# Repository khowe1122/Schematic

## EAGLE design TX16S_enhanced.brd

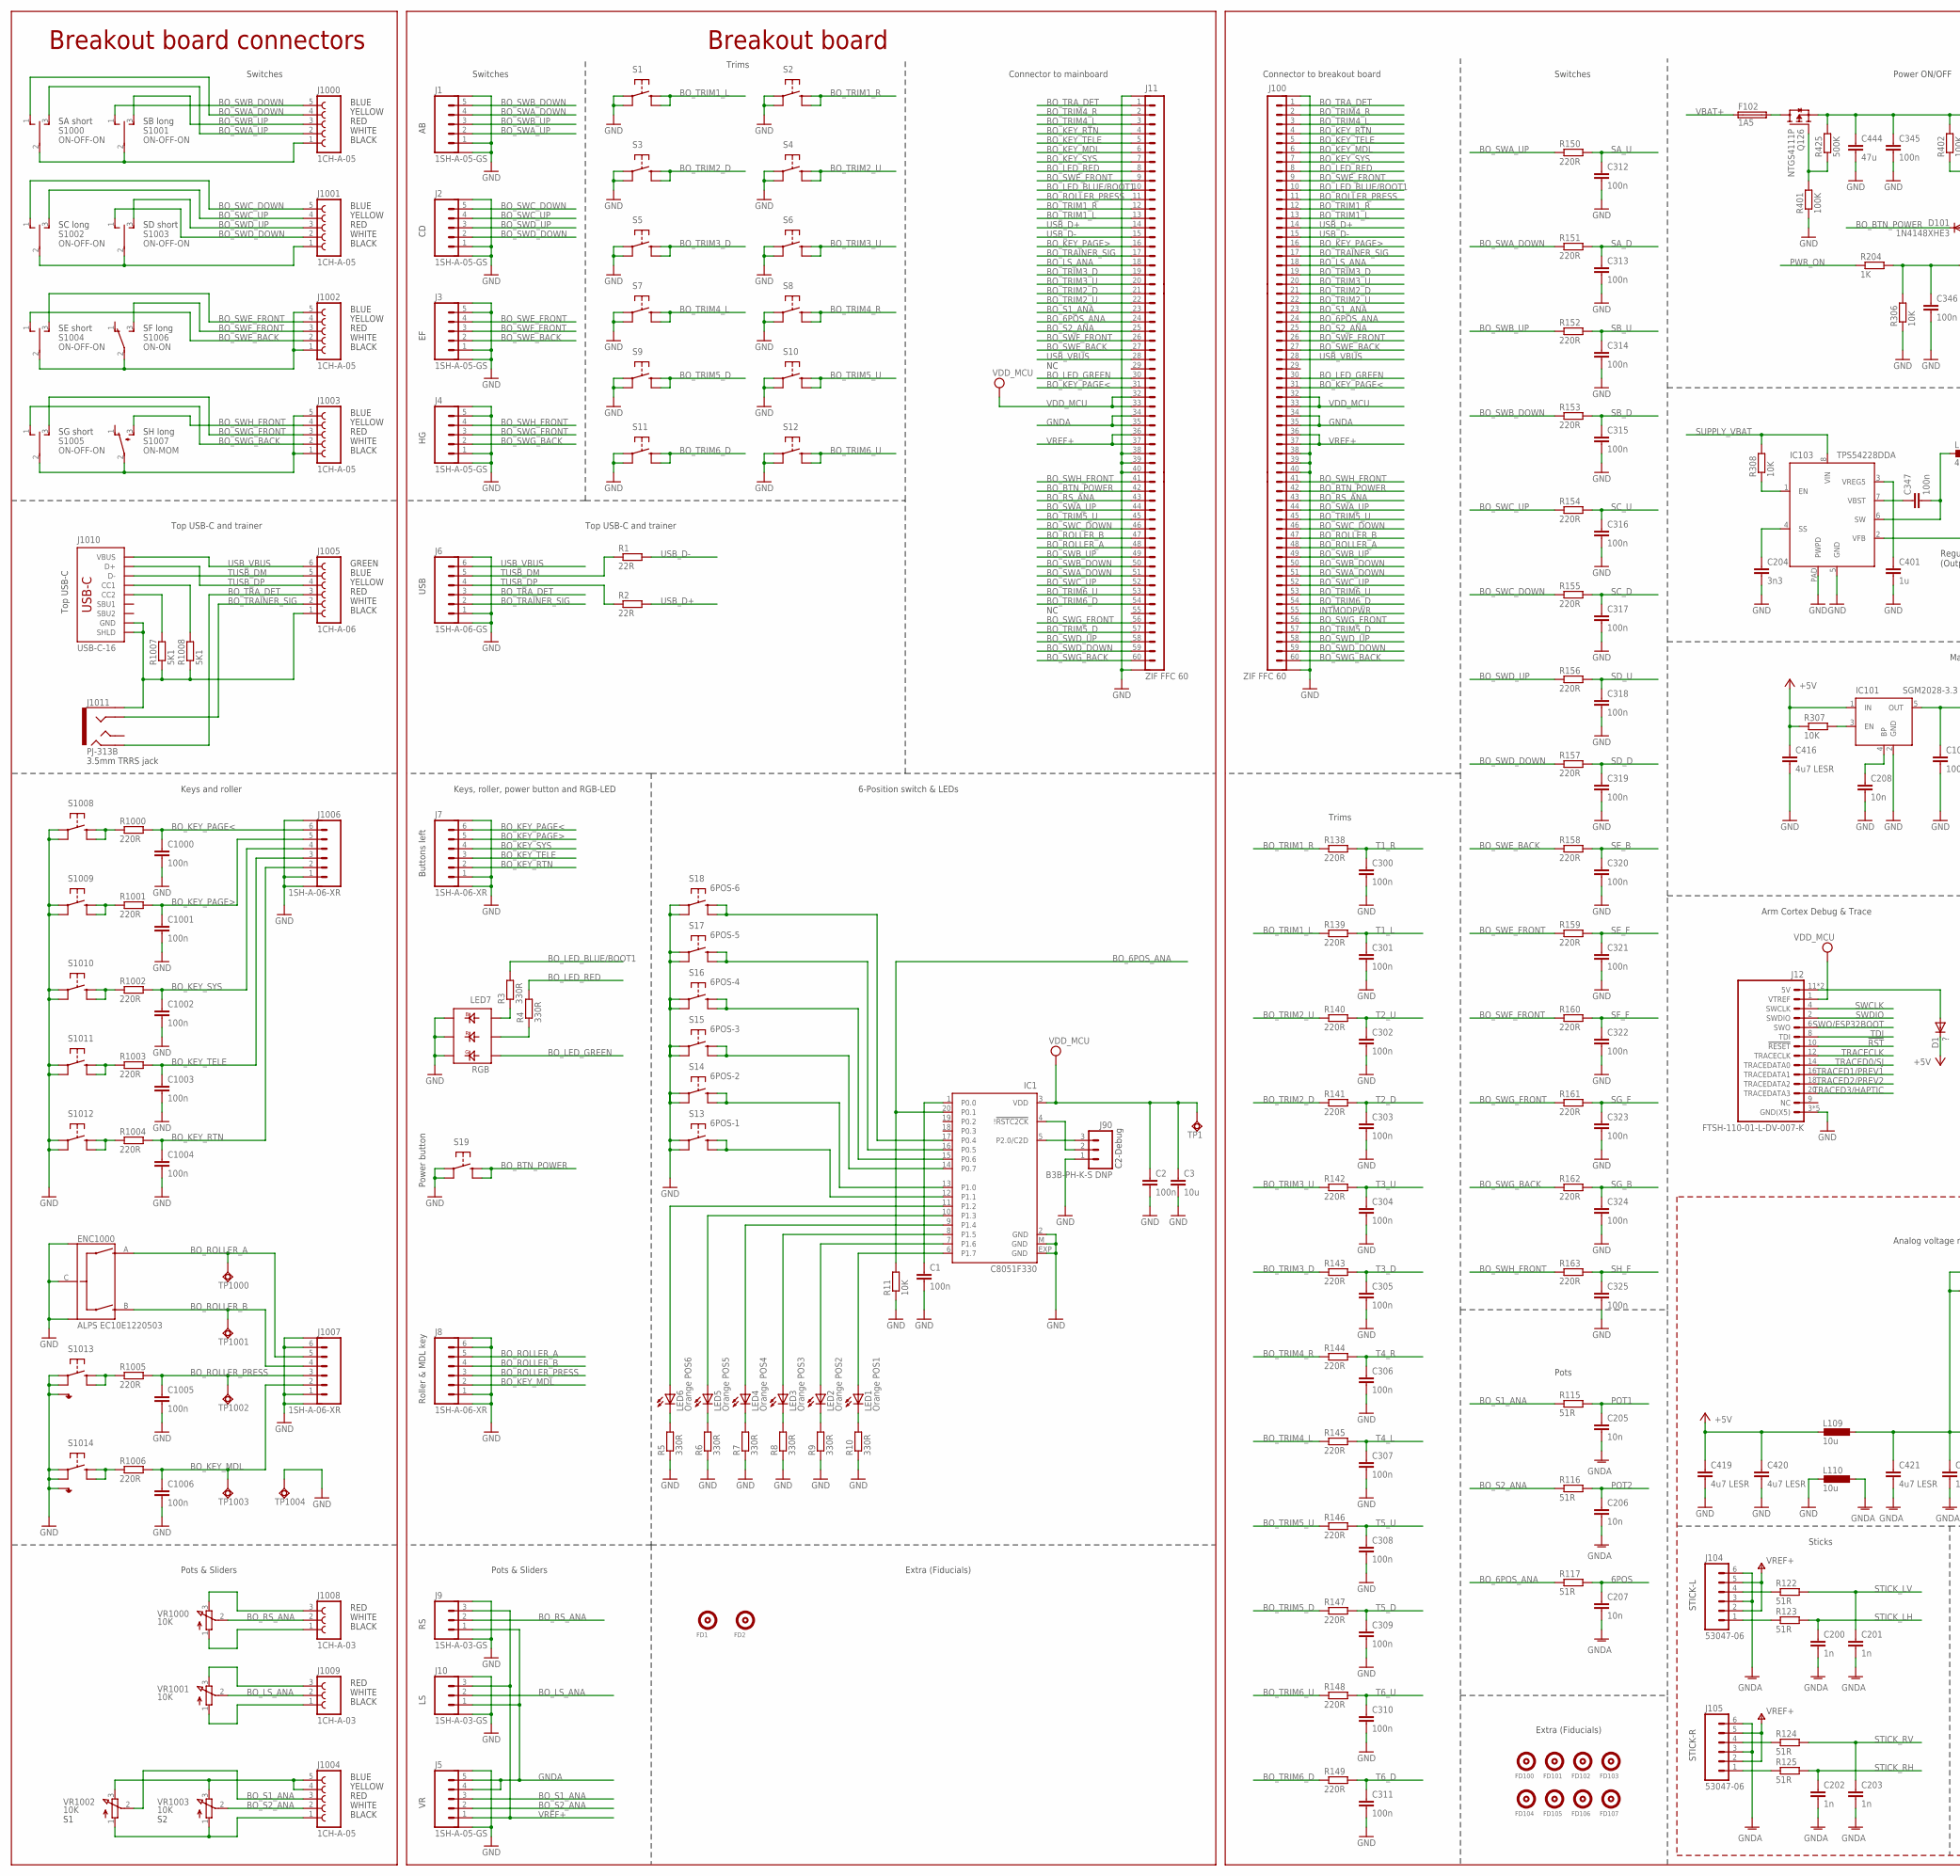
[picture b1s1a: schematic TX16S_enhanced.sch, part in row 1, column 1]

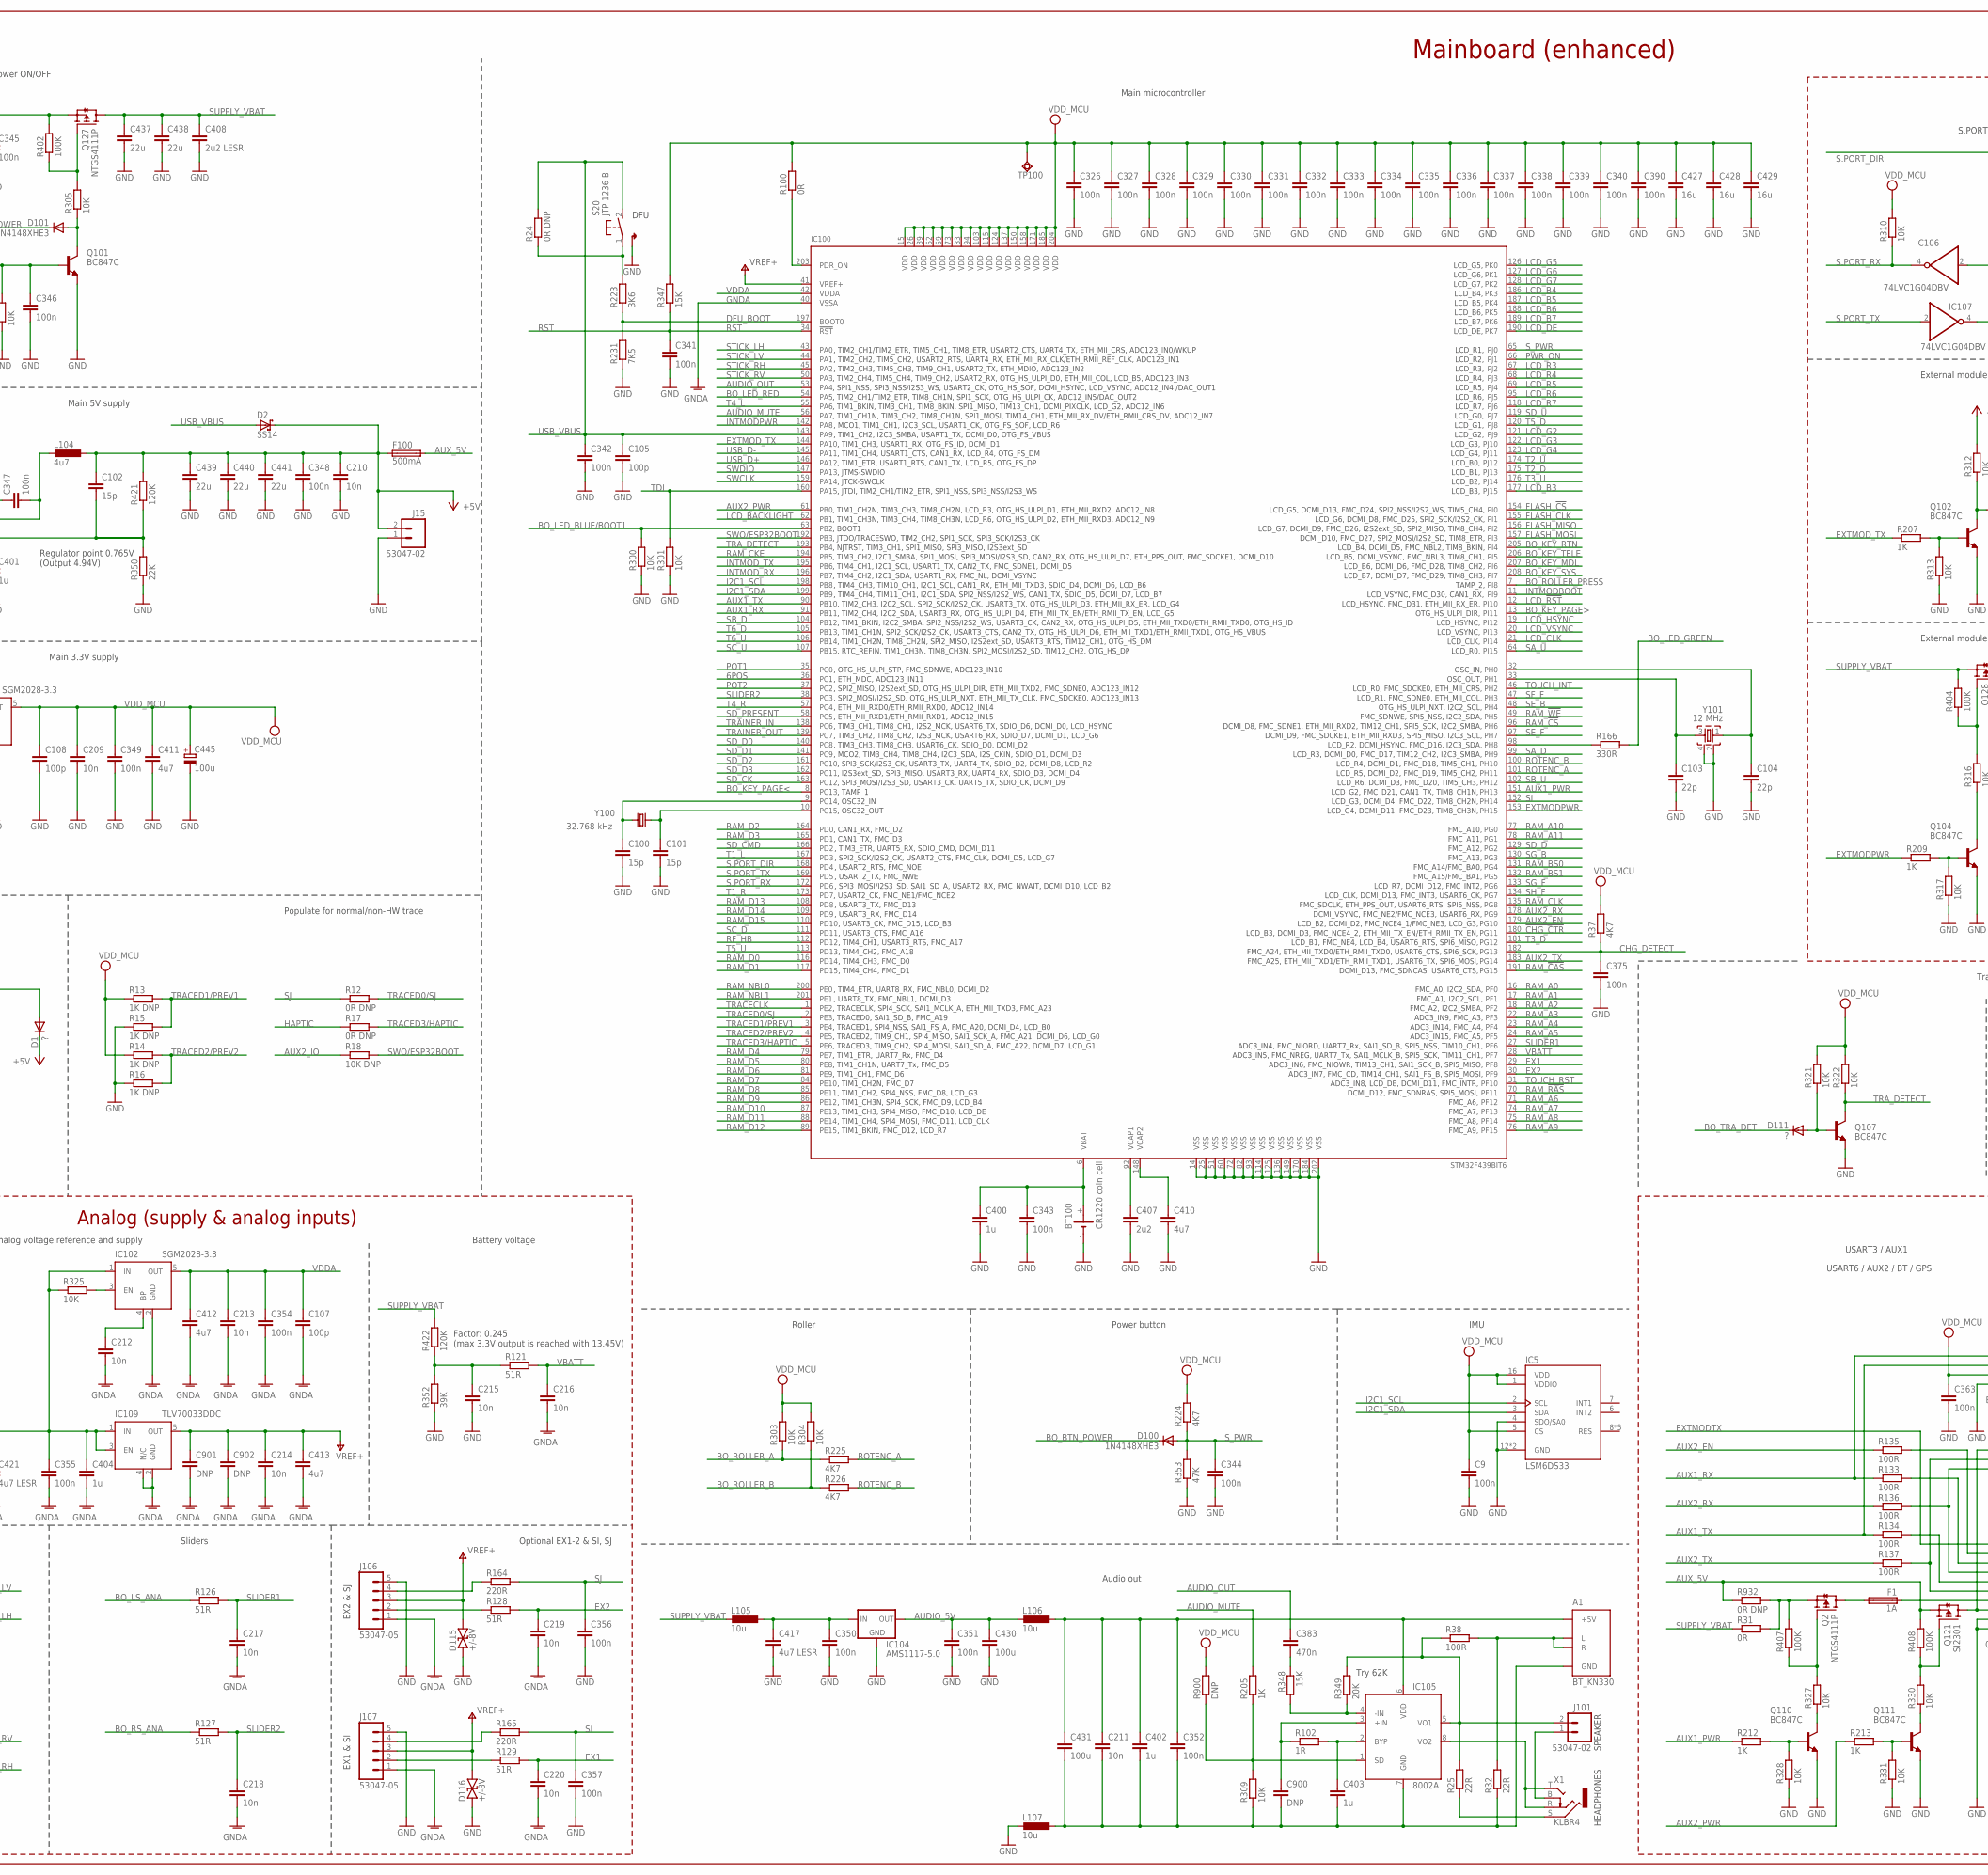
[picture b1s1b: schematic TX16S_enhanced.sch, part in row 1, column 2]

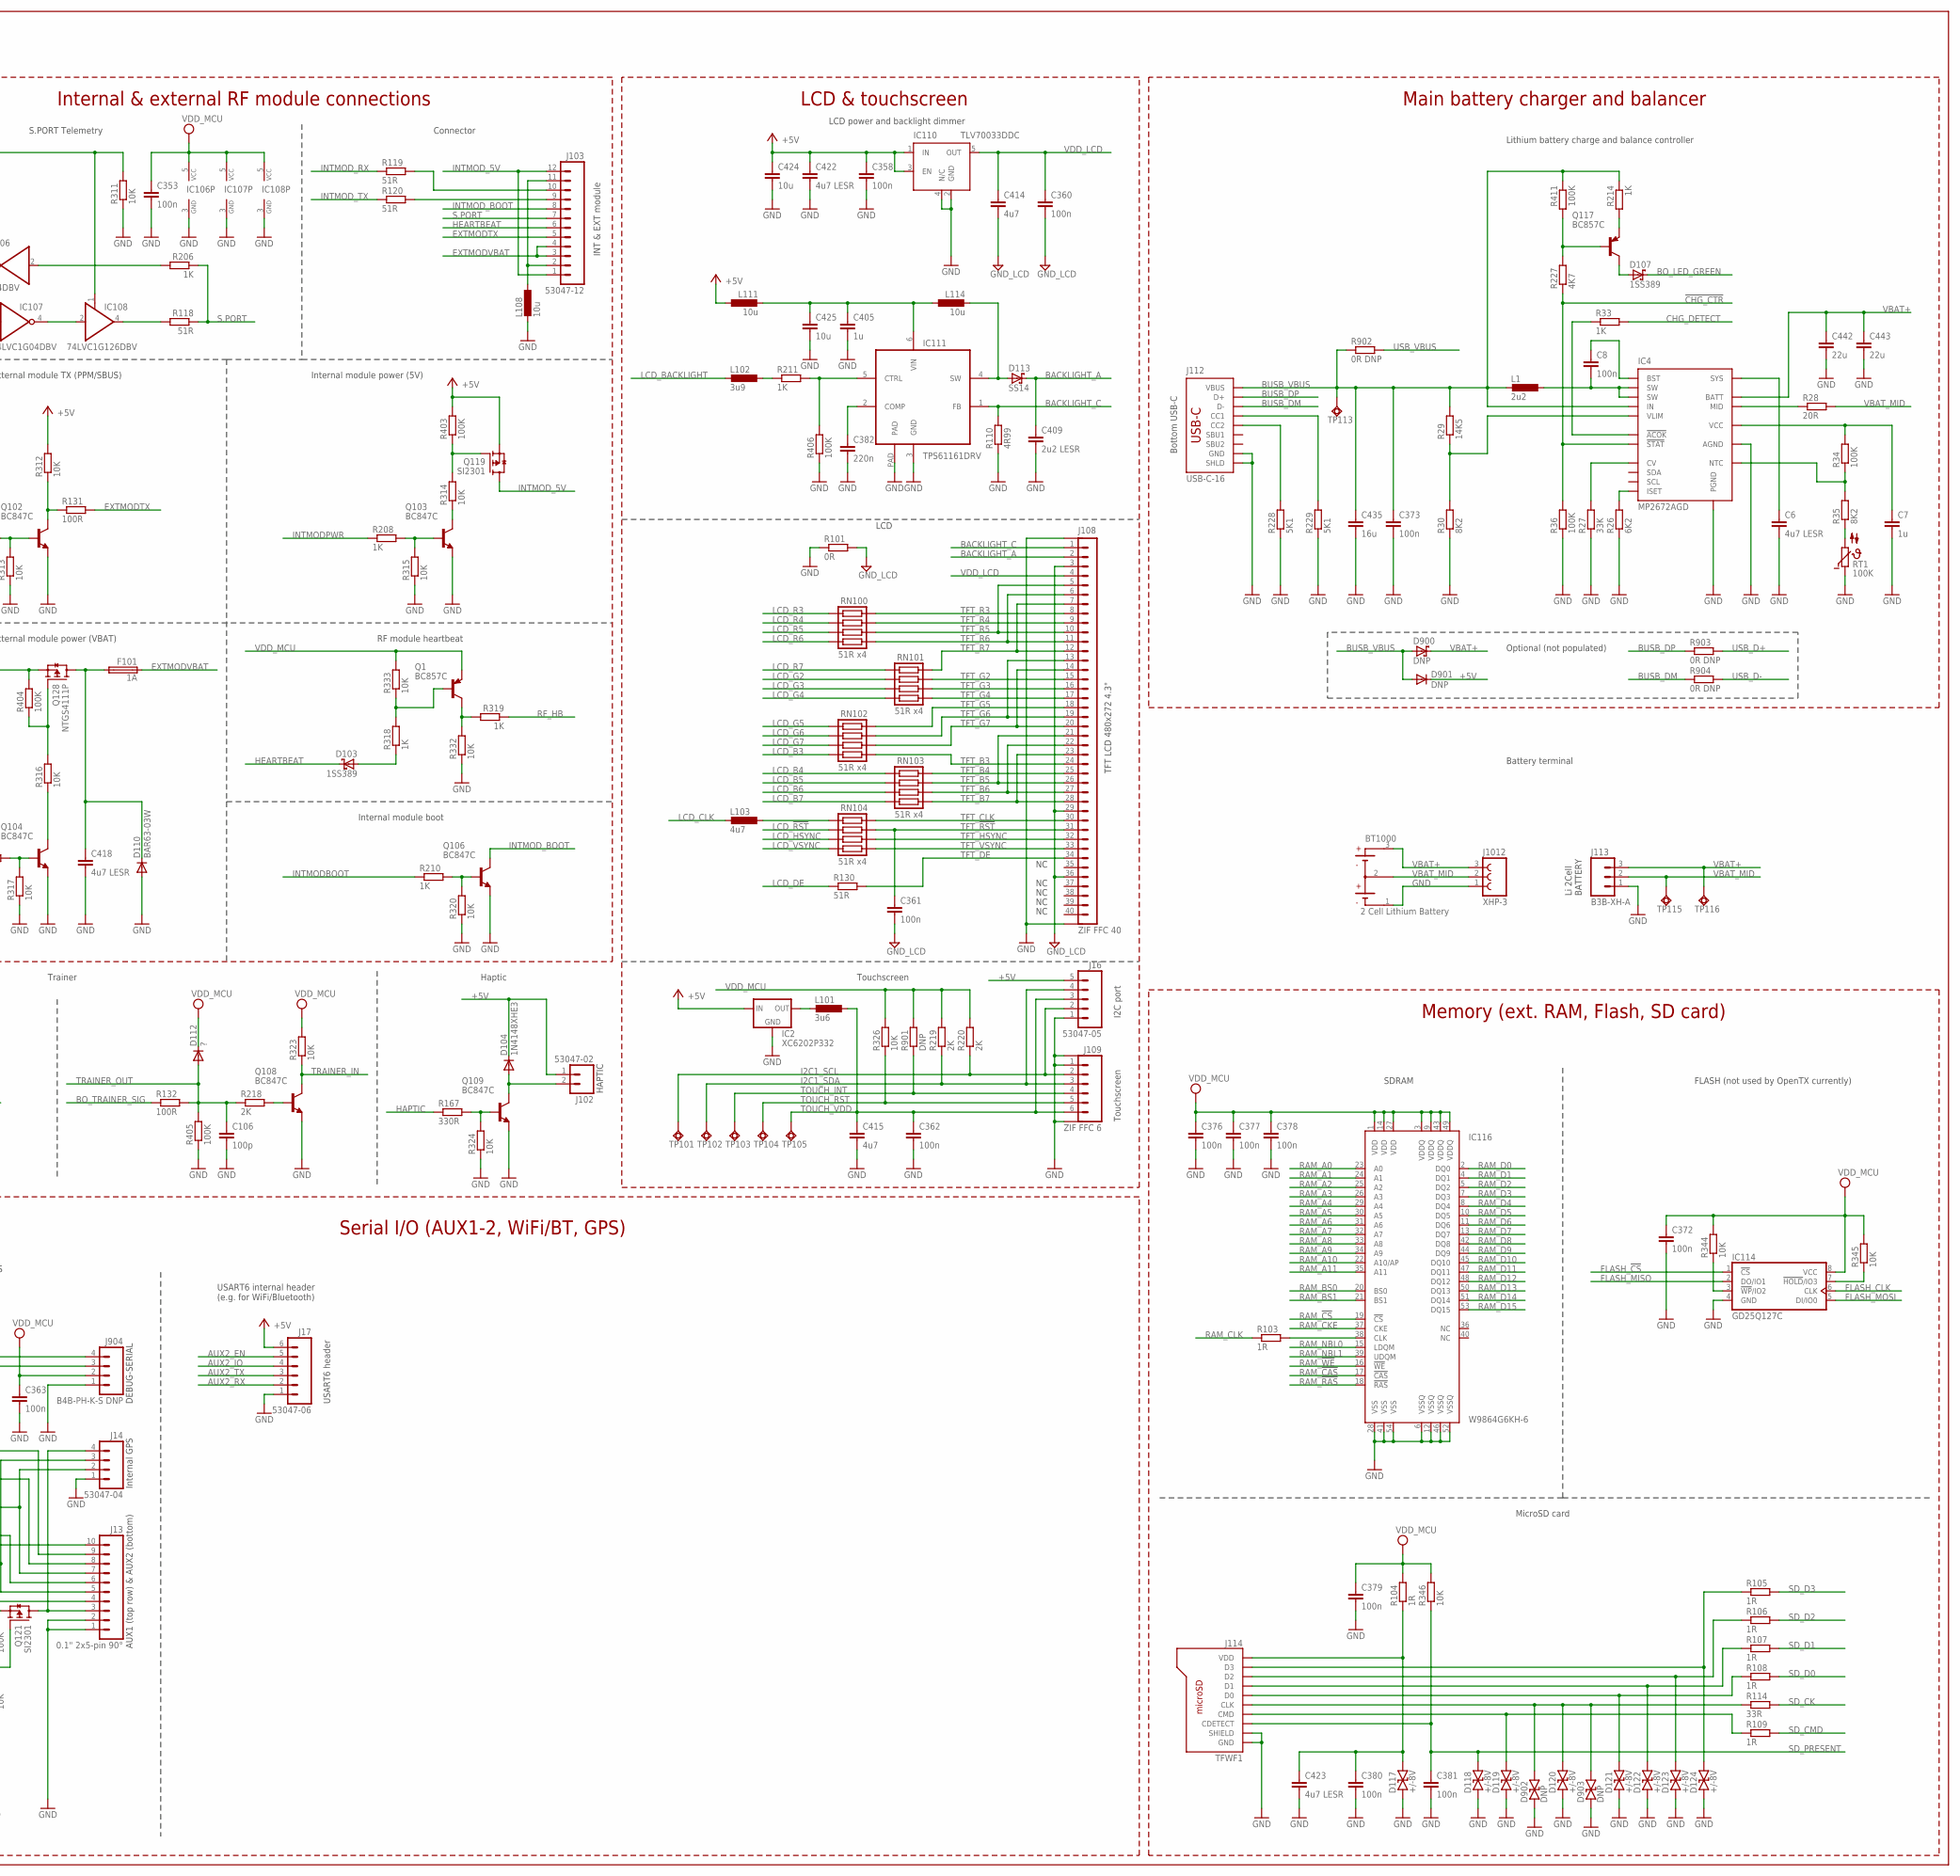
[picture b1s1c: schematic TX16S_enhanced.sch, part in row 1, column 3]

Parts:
A1: BT_KN330
BT100: CR1220 coin cell; CH291-1220LF
BT1000: 2 Cell Lithium Battery; BATTERY_2S_5000
C1, C2, C300, C301, C302, C303, C304, C305, C306, C307, C308, C309, C310, C311, C312, C313, C314, C315, C316, C317, C318, C319, C320, C321, C322, C323, C324, C325, C326, C327, C328, C329, C330, C331, C332, C333, C334, C335, C336, C337, C338, C339, C340, C341, C342, C343, C344, C345, C346, C347, C348, C349, C350, C351, C352, C354, C355, C356, C358, C360, C361, C363, C376, C377, C378, C379, C381, C390, C1000, C1001, C1002, C1003, C1004: 100n; C0402
C3: 10u; C0402
C6, C416, C417, C418, C419, C420, C421, C422, C423: 4u7 LESR; C2012
C7: 1u; C0603
C8, C9, C353, C357, C362, C372, C373, C375, C380: 100n; C0603
C100, C101, C102: 15p; C0402
C103, C104: 22p; C0402
C105, C106, C107, C108: 100p; C0402
C200, C201, C202, C203: 1n; C0402
C204: 3n3; C0402
C205, C206, C207, C208, C209, C210, C211, C212, C213, C214, C215, C216, C217, C218, C219: 10n; C0402
C220: 10n; C0603
C382: 220n; C0402
C383: 470n; C0402
C400, C401, C402, C403, C404, C405: 1u; C0402
C407: 2u2; C0402
C408, C409: 2u2 LESR; C0603
C410, C415: 4u7; C0603
C411, C412, C413, C414: 4u7; C0402
C424, C425: 10u; C2012
C427, C428, C429, C435: 16u; C2012
C430, C431: 100u; C3225
C437, C438, C439, C440, C441, C442, C443: 22u; C3216
C444: 47u; C3216
C445: 100u; SMC_D
C900, C901, C902: DNP; C0402
C1005, C1006: 100n; C0805
D1, D111, D112: ?; SOD523
D2, D113: SS14; DO-214AC
D100, D101, D104: 1N4148XHE3; SOD523
D103, D107: 1SS389; SOD523
D110: BAR63-03W; SOD323-R
D115, D116, D117, D118, D119, D120, D121, D122, D123, D124: +/-8V; DFN1006-2L
D900: DNP; DO-214AC
D901: DNP; SOD523
D902, D903: DNP; DFN1006-2L
ENC1000: ALPS EC10E1220503; APLS_EC10E
F1, F101: 1A; 1206
F100: 500mA; 1206
F102: 1A5; 1206
FD1, FD2, FD100, FD101, FD102, FD103, FD104, FD105, FD106, FD107: FIDUCIAL
IC1: C8051F330; MLP20
IC2: XC6202P332; SOT-23
IC4: MP2672AGD; MP2672A
IC5: LSM6DS33; LGA_3X3_16L
IC100: STM32F439BIT6; LQFP208
IC101, IC102: SGM2028-3.3; SOT23-5
IC103: TPS54228DDA; HSOP-8
IC104: AMS1117-5.0; SOT-223
IC105: 8002A; SOP-8
IC106, IC107: 74LVC1G04DBV; SOT23-5
IC108: 74LVC1G126DBV; SOT23-5
IC109, IC110: TLV70033DDC; SOT23-5
IC111: TPS61161DRV; WSON6
IC114: GD25Q127C; SOP-8_208MIL
IC116: W9864G6KH-6; TSOP_II_54
J1, J2, J3, J4, J5: 1SH-A-05-GS; AT_1SH-A-05-XS
J6: 1SH-A-06-GS; AT_1SH-A-06-XS
J7, J8: 1SH-A-06-XR; AT_1SH-A-06-XR
J9, J10: 1SH-A-03-GS; AT_1SH-A-03-XS
J11: ZIF FFC 60; CON-FFC-60-REV
J12: FTSH-110-01-L-DV-007-K; FTSH-110
J13: 0.1" 2x5-pin 90°; PH2.54-5W2
J14: 53047-04; MOLEX_53047-04
J15, J101, J102: 53047-02; MOLEX_53047-02
J16, J106, J107: 53047-05; MOLEX_53047-05
J17, J104, J105: 53047-06; MOLEX_53047-06
J90: B3B-PH-K-S DNP; JST_B3B_PH-K-S
J100: ZIF FFC 60; CON-FFC-60
J103: 53047-12; MOLEX_53047-12
J108: ZIF FFC 40; CON-FFC-40
J109: ZIF FFC 6; CON-FFC-6
J112, J1010: USB-C-16
J113: B3B-XH-A; JST_B3B-XH-A
J114: TFWF1
J904: B4B-PH-K-S DNP; JST_B4B_PH-K-S
J1000, J1001, J1002, J1003, J1004: 1CH-A-05; PADS_5_1MM
J1005: 1CH-A-06; PADS_6_1MM
J1006, J1007: 1SH-A-06-XR; AT_1SH-A-06-XR-REV
J1008, J1009: 1CH-A-03; PADS_3_1MM
J1011: PJ-313B
J1012: XHP-3; JST_XHP-3
L1: 2u2; PIS2816
L101: 3u6; 0603
L102: 3u9; 0603
L103: 4u7; 0603
L104: 4u7; PIS2816
L105, L106, L107: 10u; L3225M
L108, L109, L110, L111: 10u; 0603
L114: 10u; PIS2816
LED1: Orange POS1; SML0603
LED2: Orange POS2; SML0603
LED3: Orange POS3; SML0603
LED4: Orange POS4; SML0603
LED5: Orange POS5; SML0603
LED6: Orange POS6; SML0603
LED7: RGB; PLCC-6
Q1, Q117: BC857C; SOT-23
Q2, Q126, Q127, Q128: NTGS4111P; TSOP-6
Q101, Q102, Q103, Q104, Q106, Q107, Q108, Q109, Q110, Q111: BC847C; SOT-23
Q119, Q121: SI2301; SOT-23
R1, R2: 22R; R0402
R3, R4, R5, R6, R7, R8, R9, R10, R166, R167: 330R; R0402
R11, R300, R303, R304, R305, R306, R307, R308, R309, R313, R314, R315, R317, R321, R322, R323, R324, R325, R332, R333, R346: 10K; R0402
R12, R17, R24, R903, R904: 0R DNP; R0402
R13, R14, R15, R16: 1K DNP; R0402
R18: 10K DNP; R0603
R25: 22R; R1206
R26: 6K2; R0603
R27: 33K; R0603
R28: 20R; R2010
R29: 14K5; R0603
R30, R35: 8K2; R0603
R31, R101: 0R; R0603
R32: 22R; R0603
R33, R212, R213: 1K; R0603
R34, R36, R404, R407, R408: 100K; R0603
R37: 4K7; R0603
R38, R131, R133, R134: 100R; R0603
R100: 0R; R0402
R102, R103, R104, R105, R106, R107, R108, R109: 1R; R0402
R110: 4R99; R0805
R114: 33R; R0402
R115, R116, R117, R118, R119, R120, R121, R122, R123, R124, R125, R126, R127, R128, R130: 51R; R0402
R129: 51R; R0603
R132, R135, R136, R137: 100R; R0402
R138, R139, R140, R141, R142, R143, R144, R145, R146, R147, R148, R149, R150, R151, R152, R153, R154, R155, R156, R157, R158, R159, R160, R161, R162, R163, R164, R1000, R1001, R1002, R1003, R1004: 220R; R0402
R165: 220R; R0603
R204, R205, R206, R207, R208, R209, R210, R211, R214, R318, R319: 1K; R0402
R218: 2K; R0402
R219, R220: 2K; R0603
R223: 3K6; R0402
R224, R225, R226, R227: 4K7; R0402
R228, R229, R1007, R1008: 5K1; R0402
R231: 7K5; R0402
R301, R310, R311, R312, R316, R320, R326, R327, R328, R330, R331, R344, R345: 10K; R0603
R347, R348: 15K; R0402
R349: 20K; R0402
R350: 22K; R0402
R352: 39K; R0402
R353: 47K; R0402
R401, R402, R403, R405, R406, R411: 100K; R0402
R421, R422: 120K; R0402
R425: 500K; R0402
R900: DNP; R0402
R901: DNP; R0603
R902, R932: 0R DNP; R0603
R1005, R1006: 220R; R0805
RN100, RN101, RN102, RN103, RN104: 51R x4; EXB38V
RT1: 100K; NTC_3MM
S1, S2, S3, S4, S5, S6, S7, S8, S9, S10, S11, S12, S19, S1008, S1009, S1010, S1011, S1012: TX16S_BUTTON
S13: 6POS-1; TX16S_BUTTON
S14: 6POS-2; TX16S_BUTTON
S15: 6POS-3; TX16S_BUTTON
S16: 6POS-4; TX16S_BUTTON
S17: 6POS-5; TX16S_BUTTON
S18: 6POS-6; TX16S_BUTTON
S20: JTP 1236 B; JTP1236B
S1000, S1001, S1002, S1003, S1004, S1005: ON-OFF-ON; TL3XPO
S1006: ON-ON; TL3XPO
S1007: ON-MOM; TL3XPO
S1013: TX16S_BUTTON2B; TX16S_BUTTON2
S1014: TX16S_BUTTON2A; TX16S_BUTTON2
TP1, TP100, TP115, TP116, TP1000, TP1001, TP1002, TP1003: TPSQTP11R; TP11R
TP101, TP102, TP103, TP104, TP105, TP113: TPSQTP10R; TP10R
TP1004: TPSQTP15R; TP15R
VR1000, VR1001, VR1002, VR1003: 10K; EVUFXL
X1: KLBR4
Y100: 32.768 kHz; 3215
Y101: 12 MHz; 3225

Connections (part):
5V: D1.A, J12.11 (5V), J12.13 (5V)
6POS: C207.1, IC100.36 (PC1), R117.2
6PS1: IC1.12 (P1.1), S13.2.1, S13.2.2
6PS2: IC1.13 (P1.0), S14.2.1, S14.2.2
6PS3: IC1.14 (P0.7), S15.2.1, S15.2.2
6PS4: IC1.15 (P0.6), S16.2.1, S16.2.2
6PS5: IC1.16 (P0.5), S17.2.1, S17.2.2
6PS6: IC1.17 (P0.4), S18.2.1, S18.2.2
!CHG_CTR: IC4.16 (!STAT), IC100.180 (PG11), R36.2, R227.1
!RST: C341.1, IC100.34 (!RST), J12.10 (!RESET), R347.1
+5V: C102.1, C210.1, C348.1, C358.1, C416.1, C419.1, C420.1, C422.1, C424.1, C439.1, C440.1, C441.1, D1.C, D2.C, D104.C, D901.C, F100.1, IC2.3 (IN), IC101.1 (IN), IC110.1 (IN), IC110.3 (EN), J15.2, J16.5, J17.6, J102.1, L104.1, L109.2, L111.1, Q119.2 (S), R307.1, R312.2, R403.2, R421.2
AUDIO_5V: C351.1, C430.1, IC104.2 (OUT), IC104.4 (OUT), L106.2
AUDIO_GND: A1.GND, C211.2, C352.2, C402.2, C403.2, C431.2, C900.2, IC105.7 (GND), L107.1, R32.1, R309.1
AUDIO_MUTE: IC100.56 (PA7), R205.2
AUDIO_OUT: C383.1, IC100.53 (PA4)
AUX1_PWR: IC100.151 (PH13), R212.1
AUX1_RX: IC100.91 (PB11), J904.4, R133.1
AUX1_TX: IC100.90 (PB10), J904.3, R134.1
AUX2_EN: IC100.179 (PG10), J17.5, R135.1
AUX2_IO: J17.4, R18.1
AUX2_PWR: IC100.61 (PB0), R213.1
AUX2_RX: IC100.178 (PG9), J17.2, R136.1
AUX2_TX: IC100.183 (PG14), J17.3, R137.1
AUX_5V: F100.2, Q121.2 (S), R408.2, R932.1
BACKLIGHT_A: C409.1, D113.C, J108.2
BACKLIGHT_C: IC111.1 (FB), J108.1, R110.2
BO_6POS_ANA: IC1.20 (P0.1), J11.24, J100.24, R11.2, R117.1
BO_BTN_POWER: D100.C, D101.C, J11.42, J100.42, S19.2.1, S19.2.2
BO_KEY_MDL: C1006.1, IC100.207 (PI6), J8.2, J11.6, J100.6, J1007.2, R1006.2, TP1003.TP
BO_KEY_PAGE<: C1000.1, IC100.8 (PC13), J7.6, J11.31, J100.31, J1006.6, R1000.2
BO_KEY_PAGE>: C1001.1, IC100.13 (PI11), J7.5, J11.16, J100.16, J1006.5, R1001.2
BO_KEY_RTN: C1004.1, IC100.205 (PI4), J7.2, J11.4, J100.4, J1006.2, R1004.2
BO_KEY_SYS: C1002.1, IC100.208 (PI7), J7.4, J11.7, J100.7, J1006.4, R1002.2
BO_KEY_TELE: C1003.1, IC100.206 (PI5), J7.3, J11.5, J100.5, J1006.3, R1003.2
BO_LED_BLUE/BOOT1: IC100.63 (PB2), J11.10, J100.10, R3.2, R300.2
BO_LED_GREEN: D107.C, J11.30, J100.30, LED7.AG (GRN-A), R166.2
BO_LED_RED: IC100.54 (PA5), J11.8, J100.8, R4.2
BO_LS_ANA: J10.2, J11.18, J100.18, J1009.2, R126.1, VR1001.2 (S)
BO_ROLLER_A: ENC1000.A, J8.5, J11.48, J100.48, J1007.5, R225.1, R303.1, TP1000.TP
BO_ROLLER_B: ENC1000.B, J8.4, J11.47, J100.47, J1007.4, R226.1, R304.1, TP1001.TP
BO_ROLLER_PRESS: C1005.1, IC100.7 (PI8), J8.3, J11.11, J100.11, J1007.3, R1005.2, TP1002.TP
BO_RS_ANA: J9.2, J11.43, J100.43, J1008.2, R127.1, VR1000.2 (S)
BO_S1_ANA: J5.3, J11.23, J100.23, J1004.3, R115.1, VR1002.2 (S)
BO_S2_ANA: J5.2, J11.25, J100.25, J1004.2, R116.1, VR1003.2 (S)
BO_SWA_DOWN: J1.4, J11.51, J100.51, J1000.4, R151.1, S1000.1 (O)
BO_SWA_UP: J1.2, J11.44, J100.44, J1000.2, R150.1, S1000.3 (S)
BO_SWB_DOWN: J1.5, J11.50, J100.50, J1000.5, R153.1, S1001.1 (O)
BO_SWB_UP: J1.3, J11.49, J100.49, J1000.3, R152.1, S1001.3 (S)
BO_SWC_DOWN: J2.5, J11.46, J100.46, J1001.5, R155.1, S1002.1 (O)
BO_SWC_UP: J2.4, J11.52, J100.52, J1001.4, R154.1, S1002.3 (S)
BO_SWD_DOWN: J2.2, J11.59, J100.59, J1001.2, R157.1, S1003.1 (O)
BO_SWD_UP: J2.3, J11.58, J100.58, J1001.3, R156.1, S1003.3 (S)
BO_SWE_BACK: J3.2, J11.27, J100.27, J1002.2, R158.1, S1004.1 (O)
BO_SWE_FRONT: J3.4, J11.9, J100.9, J1002.4, R159.1, S1004.3 (S)
BO_SWF_FRONT: J3.3, J11.26, J100.26, J1002.3, R160.1, S1006.3 (S)
BO_SWG_BACK: J4.2, J11.60, J100.60, J1003.2, R162.1, S1005.1 (O)
BO_SWG_FRONT: J4.3, J11.56, J100.56, J1003.3, R161.1, S1005.3 (S)
BO_SWH_FRONT: J4.4, J11.41, J100.41, J1003.4, R163.1, S1007.3 (S)
BO_TRAINER_SIG: J6.2, J11.17, J100.17, J1005.2, J1011.4, R132.1
BO_TRA_DET: D111.C, J6.3, J11.1, J100.1, J1005.3, J1011.3
BO_TRIM1_L: J11.13, J100.13, R139.1, S1.2.1, S1.2.2
BO_TRIM1_R: J11.12, J100.12, R138.1, S2.2.1, S2.2.2
BO_TRIM2_D: J11.21, J100.21, R141.1, S3.2.1, S3.2.2
BO_TRIM2_U: J11.22, J100.22, R140.1, S4.2.1, S4.2.2
BO_TRIM3_D: J11.19, J100.19, R143.1, S5.2.1, S5.2.2
BO_TRIM3_U: J11.20, J100.20, R142.1, S6.2.1, S6.2.2
BO_TRIM4_L: J11.3, J100.3, R145.1, S7.2.1, S7.2.2
BO_TRIM4_R: J11.2, J100.2, R144.1, S8.2.1, S8.2.2
BO_TRIM5_D: J11.57, J100.57, R147.1, S9.2.1, S9.2.2
BO_TRIM5_U: J11.45, J100.45, R146.1, S10.2.1, S10.2.2
BO_TRIM6_D: J11.54, J100.54, R149.1, S11.2.1, S11.2.2
BO_TRIM6_U: J11.53, J100.53, R148.1, S12.2.1, S12.2.2
BUSB_DM: J112.A7 (D-), J112.B7 (D-), R904.1
BUSB_DP: J112.A6 (D+), J112.B6 (D+), R903.1
BUSB_VBUS: C373.1, C435.1, D900.A, D901.A, IC4.1 (IN), J112.VBUS1 (VBUS), J112.VBUS2 (VBUS), L1.2, R29.2, R214.1, R411.1, R902.1, TP113.TP
C2CK: IC1.4 (!!RSTC2CK), J90.2
C2D: IC1.5 (P2.0/C2D), J90.3
CHG_DETECT: C375.1, IC100.182 (PG13), R33.2, R37.1
DFU_BOOT: IC100.197 (BOOT0), R223.1, R231.2
EX1: C220.1, IC100.29 (PF8), R129.2
EX2: C219.1, IC100.30 (PF9), R128.2
EXTMODPWR: IC100.153 (PH15), R209.1
EXTMODTX: J13.10, J103.5, R131.2
EXTMODVBAT: F101.1, J103.3, J103.4
EXTMOD_TX: IC100.144 (PA10), R207.1
FLASH_!CS: IC100.154 (PI0), IC114.1 (!CS!)
FLASH_CLK: IC100.155 (PI1), IC114.6 (CLK)
FLASH_MISO: IC100.156 (PI2), IC114.2 (DO/IO1)
FLASH_MOSI: IC100.157 (PI3), IC114.5 (DI/IO0)
GND: BT100.-, BT1000.1 (JST-), C1.2, C2.2, C3.2, C6.2, C7.2, C9.2, C100.2, C101.2, C103.2, C104.2, C105.2, C106.2, C108.2, C204.2, C208.2, C209.2, C210.2, C215.2, C300.2, C301.2, C302.2, C303.2, C304.2, C305.2, C306.2, C307.2, C308.2, C309.2, C310.2, C311.2, C312.2, C313.2, C314.2, C315.2, C316.2, C317.2, C318.2, C319.2, C320.2, C321.2, C322.2, C323.2, C324.2, C325.2, C326.2, C327.2, C328.2, C329.2, C330.2, C331.2, C332.2, C333.2, C334.2, C335.2, C336.2, C337.2, C338.2, C339.2, C340.2, C341.2, C342.2, C343.2, C344.2, C345.2, C346.2, C348.2, C349.2, C350.2, C351.2, C353.2, C356.2, C357.2, C358.2, C362.2, C363.2, C372.2, C373.2, C375.2, C376.2, C377.2, C378.2, C379.2, C380.2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
GNDA: C107.2, C200.2, C201.2, C202.2, C203.2, C205.2, C206.2, C207.2, C212.2, C213.2, C214.2, C216.2, C217.2, C218.2, C219.2, C220.2, C354.2, C355.2, C404.2, C412.2, C413.2, C421.2, C901.2, C902.2, IC100.40 (VSSA), IC102.2 (GND), IC109.2 (GND), IC109.4 (N/C), J5.4, J5.5, J9.1, J10.1, J11.34, J11.35, J100.34, J100.35, J104.3, J104.6, J105.3, J105.6, J106.1, J107.1, J1004.4, J1004.5, J1008.1, J1009.1, L110.1, VR1000.1 (A), VR1001.1 (A), VR1002.3 (E), VR1003.3 (E)
GND_LCD: C360.2, C361.2, C414.2, J108.3, J108.29, J108.36, R101.2
HAPTIC: R17.1, R167.1
HEARTBEAT: D103.C, J103.6
I2C1_SCL: IC5.2 (SCL), IC100.198 (PB8), J16.2, J109.2, R220.1, TP101.TP
I2C1_SDA: IC5.3 (SDA), IC100.199 (PB9), J16.4, J109.3, R219.1, TP102.TP
INTMODBOOT: IC100.11 (PI9), R210.1
INTMODPWR: IC100.142 (PA8), J100.55, R208.1
INTMOD_5V: J103.1, J103.12, Q119.3 (D)
INTMOD_BOOT: J103.8, Q106.3 (C)
INTMOD_RX: IC100.196 (PB7), R119.1
INTMOD_TX: IC100.195 (PB6), R120.1
LCD_!RST: IC100.12 (PI10), RN104.2A
LCD_B3: IC100.177 (PJ15), RN102.4A
LCD_B4: IC100.186 (PK3), RN103.1A
LCD_B5: IC100.187 (PK4), RN103.2A
LCD_B6: IC100.188 (PK5), RN103.3A
LCD_B7: IC100.189 (PK6), RN103.4A
LCD_BACKLIGHT: IC100.62 (PB1), L102.2
LCD_CLK: IC100.21 (PI14), L103.2
LCD_DE: IC100.190 (PK7), R130.1
LCD_G2: IC100.121 (PJ9), RN101.2A
LCD_G3: IC100.122 (PJ10), RN101.3A
LCD_G4: IC100.123 (PJ11), RN101.4A
LCD_G5: IC100.126 (PK0), RN102.1A
LCD_G6: IC100.127 (PK1), RN102.2A
LCD_G7: IC100.128 (PK2), RN102.3A
LCD_HSYNC: IC100.19 (PI12), RN104.3A
LCD_R3: IC100.67 (PJ2), RN100.1A
LCD_R4: IC100.68 (PJ3), RN100.2A
LCD_R5: IC100.69 (PJ4), RN100.3A
LCD_R6: IC100.95 (PJ5), RN100.4A
LCD_R7: IC100.118 (PJ6), RN101.1A
LCD_VSYNC: IC100.20 (PI13), RN104.4A
LEDPOS1: IC1.6 (P1.7), LED1.A
LEDPOS2: IC1.7 (P1.6), LED2.A
LEDPOS3: IC1.8 (P1.5), LED3.A
LEDPOS4: IC1.9 (P1.4), LED4.A
LEDPOS5: IC1.10 (P1.3), LED5.A
LEDPOS6: IC1.11 (P1.2), LED6.A
unnamed: IC116.38 (CLK), R103.2
unnamed: C407.1, IC100.92 (VCAP1)
unnamed: Q1.3 (C), R319.2, R332.2
unnamed: D113.A, IC111.4 (SW), L114.2
unnamed: IC100.98 (PH8), R166.1
unnamed: Q1.1 (B), R318.2, R333.1
unnamed: C382.1, IC111.2 (COMP)
unnamed: IC107.4 (O), IC108.2 (I)
unnamed: IC108.4 (O), R118.2
unnamed: IC106.2 (I), R206.2
unnamed: IC114.3 (!WP!/IO2), R344.1
unnamed: IC114.7 (!HOLD!/IO3), R345.1
unnamed: C1.1, IC1.1 (P0.0)
unnamed: J103.2, J103.11, L108.1
unnamed: J103.9, R120.2
unnamed: LED1.C, R10.2
unnamed: LED2.C, R9.2
unnamed: LED4.C, R7.2
unnamed: LED3.C, R8.2
unnamed: LED5.C, R6.2
unnamed: R1004.1, S1012.2.1, S1012.2.2
unnamed: R1003.1, S1011.2.1, S1011.2.2
unnamed: LED6.C, R5.2
unnamed: R1002.1, S1010.2.1, S1010.2.2
unnamed: Q119.1 (G), R314.2, R403.1
unnamed: Q2.4 (S), R31.2, R407.2, R932.2
unnamed: F1.2, Q2.1 (D), Q2.2 (D), Q2.5 (D), Q2.6 (D)
unnamed: A1.L, A1.R, R32.2, R38.2
unnamed: J112.A5 (CC1), R229.2
unnamed: J1010.B5 (CC2), R1007.2
unnamed: J1010.A5 (CC1), R1008.2
unnamed: R1001.1, S1009.2.1, S1009.2.2
unnamed: R1000.1, S1008.2.1, S1008.2.2
unnamed: R1006.1, S1014.2.1, S1014.2.2
unnamed: R1005.1, S1013.1.1 (2.1), S1013.1.2 (2.2)
unnamed: LED7.AB (BLU-A), R3.1
unnamed: J112.B5 (CC2), R228.2
unnamed: LED7.AR (RED-A), R4.1
unnamed: C405.1, C425.1, IC111.6 (VIN), L111.2, L114.1
unnamed: IC101.3 (EN), R307.2
unnamed: Q103.3 (C), R314.1
unnamed: Q103.1 (B), R208.2, R315.2
unnamed: D104.A, J102.2, Q109.3 (C)
unnamed: IC111.5 (CTRL), R211.2, R406.2
unnamed: L102.1, R211.1
unnamed: Q109.1 (B), R167.2, R324.2
unnamed: C346.1, Q101.1 (B), R204.2, R306.2
unnamed: D101.A, Q101.3 (C), R305.1
unnamed: D107.A, Q117.3 (C)
unnamed: Q117.1 (B), R227.2, R411.2
unnamed: C350.1, C417.1, IC104.3 (IN), L105.1
unnamed: Q117.2 (E), R214.2
unnamed: Q128.3 (G), R316.2, R404.1
unnamed: C410.1, IC100.148 (VCAP2)
unnamed: Q104.1 (B), R209.2, R317.2
unnamed: Q104.3 (C), R316.1
unnamed: C418.1, D110.C, F101.2, Q128.1 (D), Q128.2 (D), Q128.5 (D), Q128.6 (D)
unnamed: J103.10, R119.2
unnamed: Q102.3 (C), R131.1, R312.1
unnamed: Q106.1 (B), R210.2, R320.2
unnamed: D103.A, R318.1
unnamed: Q102.1 (B), R207.2, R313.2
unnamed: F1.1, J13.4
unnamed: J13.6, R134.2
unnamed: J13.8, R133.2
unnamed: J13.3, J14.4, Q121.3 (D)
unnamed: Q121.1 (G), R330.2, R408.1
unnamed: C208.1, IC101.4 (BP)
unnamed: Q2.3 (G), R327.2, R407.1
unnamed: Q110.3 (C), R327.1
unnamed: Q110.1 (B), R212.2, R328.2
unnamed: Q111.3 (C), R330.1
unnamed: D122.P$2 (2), J114.8 (D1), R107.1
unnamed: Q111.1 (B), R213.2, R331.2
unnamed: J13.5, J14.3, R137.2
unnamed: J13.7, J14.2, R136.2
unnamed: J13.9, R135.2
unnamed: R24.1, R223.2, S20.1
unnamed: L103.1, RN104.1A
unnamed: J105.1, R125.1
unnamed: J104.1, R123.1
unnamed: J105.4, R124.1
unnamed: J107.2, R129.1
unnamed: C355.1, C404.1, C421.1, IC102.1 (IN), IC109.1 (IN), IC109.3 (EN), L109.1, R325.1
unnamed: J104.4, R122.1
unnamed: J106.4, R164.1
unnamed: J107.4, R165.1
unnamed: Q108.1 (B), R218.2
unnamed: J106.2, R128.1
unnamed: C212.1, IC102.4 (BP)
unnamed: IC102.3 (EN), R325.2
unnamed: A1.+5V, C211.1, C352.1, C402.1, C431.1, IC105.6 (VDD), L106.1
unnamed: D111.A, Q107.1 (B), R321.1
unnamed: IC105.4 (-IN), R348.2, R349.1
unnamed: C383.2, R348.1
unnamed: IC105.1 (SD), R205.1, R309.2, R900.1
unnamed: C403.1, IC105.2 (BYP), R102.2
unnamed: C900.1, IC105.3 (+IN), R102.1
unnamed: C215.1, R121.1, R352.2, R422.1
unnamed: Q127.3 (G), R305.2, R402.1
unnamed: Q126.3 (G), R401.2, R425.1
unnamed: C345.1, C444.1, Q126.4 (S), Q127.4 (S), R402.2, R425.2
unnamed: R25.1, X1.S
unnamed: IC103.1 (EN), R308.1
unnamed: C347.2, IC103.6 (SW), L104.2
unnamed: C204.1, IC103.4 (SS)
unnamed: C347.1, IC103.7 (VBST)
unnamed: C102.2, IC103.2 (VFB), R350.2, R421.1
unnamed: D121.P$2 (2), J114.7 (D0), R108.1
unnamed: J101.1, X1.B
unnamed: D120.P$2 (2), D902.P$2 (2), D903.P$2 (2), J114.5 (CLK), R114.1
unnamed: D119.P$2 (2), J114.3 (CMD), R109.1
unnamed: D124.P$2 (2), J114.2 (D3), R105.1
unnamed: D123.P$2 (2), J114.1 (D2), R106.1
unnamed: C100.1, IC100.9 (PC14), Y100.1
unnamed: C101.1, IC100.10 (PC15), Y100.2
unnamed: C103.1, IC100.33 (PH1), Y101.3
unnamed: C104.1, IC100.32 (PH0), Y101.1
unnamed: IC4.5 (ISET), R26.2
unnamed: IC4.17 (CV), R27.2
unnamed: IC4.9 (MID), R28.1
unnamed: C8.2, IC4.2 (SW), IC4.12 (SW), L1.1
unnamed: IC4.7 (VLIM), R29.1, R30.2
unnamed: IC4.18 (!ACOK), R33.1
unnamed: IC4.8 (NTC), R34.1, R35.2
unnamed: R35.1, RT1.P$2 (2)
unnamed: C8.1, IC4.3 (BST)
PDR_ON: IC100.203 (PDR_ON), R100.1
POT1: C205.1, IC100.35 (PC0), R115.2
POT2: C206.1, IC100.37 (PC2), R116.2
PWR_ON: IC100.66 (PJ1), R204.1
RAM_!CAS: IC100.191 (PG15), IC116.17 (!CAS)
RAM_!CS: IC100.96 (PH6), IC116.19 (!CS)
RAM_!RAS: IC100.70 (PF11), IC116.18 (!RAS)
RAM_!WE: IC100.49 (PH5), IC116.16 (!WE)
RAM_A0: IC100.16 (PF0), IC116.23 (A0)
RAM_A1: IC100.17 (PF1), IC116.24 (A1)
RAM_A2: IC100.18 (PF2), IC116.25 (A2)
RAM_A3: IC100.22 (PF3), IC116.26 (A3)
RAM_A4: IC100.23 (PF4), IC116.29 (A4)
RAM_A5: IC100.24 (PF5), IC116.30 (A5)
RAM_A6: IC100.71 (PF12), IC116.31 (A6)
RAM_A7: IC100.74 (PF13), IC116.32 (A7)
RAM_A8: IC100.75 (PF14), IC116.33 (A8)
RAM_A9: IC100.76 (PF15), IC116.34 (A9)
RAM_A10: IC100.77 (PG0), IC116.22 (A10/AP)
RAM_A11: IC100.78 (PG1), IC116.35 (A11)
RAM_BS0: IC100.131 (PG4), IC116.20 (BS0)
RAM_BS1: IC100.132 (PG5), IC116.21 (BS1)
RAM_CKE: IC100.194 (PB5), IC116.37 (CKE)
RAM_CLK: IC100.135 (PG8), R103.1
RAM_D0: IC100.116 (PD14), IC116.2 (DQ0)
RAM_D1: IC100.117 (PD15), IC116.4 (DQ1)
RAM_D2: IC100.164 (PD0), IC116.5 (DQ2)
RAM_D3: IC100.165 (PD1), IC116.7 (DQ3)
RAM_D4: IC100.79 (PE7), IC116.8 (DQ4)
RAM_D5: IC100.80 (PE8), IC116.10 (DQ5)
RAM_D6: IC100.81 (PE9), IC116.11 (DQ6)
RAM_D7: IC100.84 (PE10), IC116.13 (DQ7)
RAM_D8: IC100.85 (PE11), IC116.42 (DQ8)
RAM_D9: IC100.86 (PE12), IC116.44 (DQ9)
RAM_D10: IC100.87 (PE13), IC116.45 (DQ10)
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
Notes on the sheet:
Trims
Switches
Pots & Sliders
Top USB-C and trainer
SA short
SB long
BLACK
WHITE
RED
YELLOW
BLUE
SC long
SD short
SE short
SF long
SG short
SH long
GREEN
USB
6-Position switch & LEDs
3.5mm TRRS jack
Breakout board
Breakout board connectors
Connector to mainboard
Mainboard (enhanced)
Roller & MDL key
Buttons left
Keys, roller, power button and RGB-LED
Keys and roller
Connector to breakout board
SPEAKER
HAPTIC
EX2 & SJ
EX1 & SI
STICK-R
STICK-L
INT & EXT module
Top USB-C
Bottom USB-C
Li 2Cell BATTERY
